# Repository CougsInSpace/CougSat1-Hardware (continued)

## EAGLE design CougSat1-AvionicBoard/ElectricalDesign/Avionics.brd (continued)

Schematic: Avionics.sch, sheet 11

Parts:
C13, C14, C27, C33, C36, C39: 100nF 10%; 1608
C17: 10nF 10%; 1608
C21, C25: 10pF 5%; 1608
C30, C32: 15pF 1%; 1608
DS1: Green; 1608-POL
J1: CougSat Card; CARD-FULL
J4: SWD; SMD2.54-1X06-R
R4, R12: 1kΩ 0.1%; 1608
R11: 0Ω <20mΩ; 1608
RT2: 10kΩ 5%; 1608
U6: STM32L476RGT; QFP-64-1010
U8, U9: TXS0102DQM; X2SON-8
Y2: 8MHz ±10ppm; SMD-5032
Y4: 32.768kHz ±10ppm; SMD-3215

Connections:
3.3V_0: C13.1, C14.1, C27.1, C33.1, C36.1, R12.2, U6.1 (VBAT), U6.13 (VDDA/VREF+), U6.19 (VDD), U6.32 (VDD), U6.48 (VDDUSB), U6.64 (VDD), U8.1 (VCCA), U9.1 (VCCA); also elsewhere on the board
3.3V_5: C39.1, U8.8 (VCCB), U9.8 (VCCB); also elsewhere on the board
!C&DH_ADC_RESET: U6.24 (PC4); also elsewhere on the board
AGND: RT2.1; also elsewhere on the board
BUS_I2C0_IRQ: J1.A45 (BUS_I2C0_IRQ), J1.B45 (BUS_I2C0_IRQ), U6.61 (PB8); also elsewhere on the board
BUS_I2C0_SCL: J1.A44 (BUS_I2C0_SCL), J1.B44 (BUS_I2C0_SCL), U6.58 (PB6); also elsewhere on the board
BUS_I2C0_SDA: J1.A43 (BUS_I2C0_SDA), J1.B43 (BUS_I2C0_SDA), U6.59 (PB7); also elsewhere on the board
BUS_I2C1_IRQ: J1.A32 (BUS_I2C1_IRQ), J1.B32 (BUS_I2C1_IRQ), U6.33 (PB12)
BUS_I2C1_SCL: J1.A31 (BUS_I2C1_SCL), J1.B31 (BUS_I2C1_SCL), U6.34 (PB13); also elsewhere on the board
BUS_I2C1_SDA: J1.A30 (BUS_I2C1_SDA), J1.B30 (BUS_I2C1_SDA), U6.30 (PB11); also elsewhere on the board
BUS_JTAG_TCK: U8.7 (B1); also elsewhere on the board
BUS_JTAG_TDI: U8.6 (B2); also elsewhere on the board
BUS_JTAG_TDO: U9.7 (B1); also elsewhere on the board
BUS_JTAG_TMS: U9.6 (B2); also elsewhere on the board
BUS_SPI_IFJR_CS: U6.43 (PA10); also elsewhere on the board
BUS_SPI_MISO: J1.A38 (BUS_SPI_MISO), J1.B38 (BUS_SPI_MISO), U6.22 (PA6); also elsewhere on the board
BUS_SPI_MOSI: J1.A39 (BUS_SPI_MOSI), J1.B39 (BUS_SPI_MOSI), U6.21 (PA5); also elsewhere on the board
BUS_SPI_SCK: J1.A37 (BUS_SPI_SCK), J1.B37 (BUS_SPI_SCK), U6.23 (PA7); also elsewhere on the board
COM_SPI_CS: J1.A36 (!COM_SPI_CS), J1.B36 (!COM_SPI_CS), U6.9 (PC1)
COM_SPI_MISO: J1.A34 (COM_SPI_MISO), J1.B34 (COM_SPI_MISO), U6.10 (PC2)
COM_SPI_MOSI: J1.A35 (COM_SPI_MOSI), J1.B35 (COM_SPI_MOSI), U6.11 (PC3)
COM_SPI_SCK: J1.A33 (COM_SPI_SCK), J1.B33 (COM_SPI_SCK), U6.29 (PB10)
CTRL_SYNC: J1.A42 (CTRL_SYNC), J1.B42 (CTRL_SYNC), U6.39 (PC8); also elsewhere on the board
DGND: C13.2, C14.2, C17.2, C21.2, C25.2, C27.2, C30.2, C32.2, C33.2, C36.2, C39.2, J4.3 (DGND), R4.2, R11.1, U6.12 (VSSA/VREF-), U6.18 (VSS), U6.31 (VSS), U6.47 (VSS), U6.63 (VSS), U8.4 (DGND), U9.4 (DGND), Y2.2 (GND), Y2.4 (GND); also elsewhere on the board
IHU_!NRST: C17.1, J4.5 (!RST), U6.7 (!NRST)
IHU_BOOT0: R11.2, U6.60 (BOOT0)
IHU_GPIO-0: J1.A24 (GPIO-0), U6.41 (PA8)
IHU_GPIO-1: J1.A25 (GPIO-1), U6.40 (PC9)
IHU_GPIO-2: J1.A26 (GPIO-2), U6.36 (PB15)
IHU_GPIO-3: J1.A27 (GPIO-3), U6.35 (PB14)
IHU_GPIO-4: J1.A28 (GPIO-4), U6.20 (PA4)
IHU_GPIO-5: J1.A29 (GPIO-5), U6.17 (PA3)
IHU_GPIO-6: J1.A41 (GPIO-6), U6.38 (PC7)
IHU_GPIO-7: J1.B41 (GPIO-7), U6.37 (PC6)
IHU_JTCK: J4.2 (SWCLK), U6.49 (PA14), U8.3 (A2)
IHU_JTDI: U6.50 (PA15), U8.2 (A1)
IHU_JTDO: J4.6 (SWO), U6.55 (PB3), U9.2 (A1)
IHU_JTMS: J4.4 (SWDIO), U6.46 (PA13), U9.3 (A2)
IHU_LED: DS1.A, U6.42 (PA9)
IHU_LED_GND: DS1.C, R4.1
IHU_OSC_32_IN: C30.1, U6.4 (PC15), Y4.1
IHU_OSC_32_OUT: C32.1, U6.3 (PC14), Y4.2
IHU_OSC_IN: C25.1, U6.5 (PH0-OSC_IN), Y2.1
IHU_OSC_OUT: C21.1, U6.6 (PH1-OSC_OUT), Y2.3 (2)
IHU_SD_CS0: U6.15 (PA1); also elsewhere on the board
IHU_SD_CS1: U6.14 (PA0); also elsewhere on the board
IHU_SD_SW0: U6.26 (PB0); also elsewhere on the board
IHU_SD_SW1: U6.28 (PB2); also elsewhere on the board
IHU_SPI_MISO: U6.52 (PC11); also elsewhere on the board
IHU_SPI_MOSI: U6.53 (PC12); also elsewhere on the board
IHU_SPI_SCK: U6.51 (PC10); also elsewhere on the board
IHU_SWD_VSENSE: J4.1 (VSENSE), R12.1
JTAG_EN_IHU: U8.5 (OE), U9.5 (OE); also elsewhere on the board
PR_3.3V-1: J1.A2 (PR_3.3V-1), J1.B2 (PR_3.3V-1)
PR_3.3V-3: J1.A4 (PR_3.3V-3), J1.B4 (PR_3.3V-3)
PR_3.3V-4: J1.A5 (PR_3.3V-4), J1.B5 (PR_3.3V-4)
PR_3.3V-6: J1.A7 (PR_3.3V-6), J1.B7 (PR_3.3V-6)
PR_3.3V-7: J1.A8 (PR_3.3V-7), J1.B8 (PR_3.3V-7)
PR_3.3V-8: J1.A9 (PR_3.3V-8), J1.B9 (PR_3.3V-8)
PR_3.3V-9: J1.A10 (PR_3.3V-9), J1.B10 (PR_3.3V-9)
PR_3.3V-10: J1.A11 (PR_3.3V-10), J1.B11 (PR_3.3V-10)
PR_3.3V-11: J1.A12 (PR_3.3V-11), J1.B12 (PR_3.3V-11)
PR_3.3V-12: J1.A13 (PR_3.3V-12), J1.B13 (PR_3.3V-12)
PR_BATT-0: J1.A14 (PR_BATT-0), J1.B14 (PR_BATT-0)
PR_BATT-1: J1.A15 (PR_BATT-1), J1.B15 (PR_BATT-1)
PR_BATT-2: J1.A16 (PR_BATT-2), J1.B16 (PR_BATT-2)
PR_BATT-3: J1.A17 (PR_BATT-3), J1.B17 (PR_BATT-3)
PR_BATT-4: J1.A18 (PR_BATT-4), J1.B18 (PR_BATT-4)
PR_BATT-6: J1.A20 (PR_BATT-6), J1.B20 (PR_BATT-6)
TEMP_IHU: RT2.2; also elsewhere on the board

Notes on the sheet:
11B6> 3C5>
<11B6><3C5>
11B6> 12C4>
<11B6><12C4>
<11B6>
<11C6>
<11B2
11B2>
12A3>
<12A3
<12B3
<11B3>
<11B3
<11B3
11B6>
<11B6
<11B4
11B4>
<11D1 <11C1
<11D6><11D1
11D6> 11D1>
<11B2>
11B6> 3B5> 9B3>
11A5>
<11B2
11B3>
<9B6
<11C1
CAD Note: Decoupling
11B2>
11C3>
CAD Note: Thermally Connected
12C1>
12C3>
9D3>
<11D6
CAD Note: Decoupling
<11C2
12B3>
<11B6 <9C3

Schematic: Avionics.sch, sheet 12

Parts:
C1, C5, C6, C7, C8, C26, C46: 100nF 10%; 1608
C2, C4: 1µF 10%; 1608
C3: 10µF 10%; 1608
C9: 4.7µF 10%; 4028-POL
FB1: 1.5kΩ @ 100MHz; 1608
J10: IHU SD0; µSD-PUSH-PUSH
J11: IHU SD1; µSD-PUSH-PUSH
R1, R5, R6: 10kΩ 0.1%; 1608
RN1: 10kΩ 5%; 3264
RT3, RT7: 10kΩ 5%; 1608
TP1: TEST_POINT-SMD-C-1.25; SMD-C-1.25
U1: AD7291; QFN-20-4040
U2: AD8515; SOT23-5

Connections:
3.3V_0: C7.1, C26.1, C46.1, FB1.1, J10.VDD, J11.VDD, R1.2, R5.2, R6.2, U1.13 (AS1), U1.16 (VDRIVE); also elsewhere on the board
!C&DH_ADC_RESET: R1.1, U1.17 (!PD!/!RST); also elsewhere on the board
AGND: C1.2, C2.2, C3.2, C5.2, C6.2, C8.2, C9.C, RT3.1, RT7.1, U1.6 (AGND), U2.2 (V-); also elsewhere on the board
AVDD-1: C5.1, C6.1, C8.1, C9.A, FB1.2, TP1.1, U1.10 (VDD), U2.5 (V+)
AVREF-2: C1.1, C2.1, RN1.5 (C), RN1.10 (C), U2.1 (OUT), U2.4 (IN-)
BUS_I2C1_SCL: U1.15 (SCL); also elsewhere on the board
BUS_I2C1_SDA: U1.14 (SDA); also elsewhere on the board
C&DH_ADC_DCAP: C4.1, U1.8 (DCAP)
C&DH_ADC_VREF: C3.1, U1.7 (VREF), U2.3 (IN+)
DGND: C4.2, C7.2, C26.2, C46.2, J10.SW-LEVER (SW-), J10.VSS, J11.SW-LEVER (SW-), J11.VSS, U1.4 (IN6), U1.5 (IN7), U1.9 (DGND), U1.11 (AS0), U1.PAD (DGND); also elsewhere on the board
IHU_SD_CS0: J10.CD/DAT3, R5.1; also elsewhere on the board
IHU_SD_CS1: J11.CD/DAT3, R6.1; also elsewhere on the board
IHU_SD_SW0: J10.SW (SW+); also elsewhere on the board
IHU_SD_SW1: J11.SW (SW+); also elsewhere on the board
IHU_SPI_MISO: J10.DAT0, J11.DAT0; also elsewhere on the board
IHU_SPI_MOSI: J10.CMD, J11.CMD; also elsewhere on the board
IHU_SPI_SCK: J10.CLK, J11.CLK; also elsewhere on the board
TEMP_IFJR: RN1.8 (7), U1.19 (IN1); also elsewhere on the board
TEMP_IHU: RN1.9 (8), U1.18 (IN0); also elsewhere on the board
TEMP_SD_IFJR0: RN1.4, U1.2 (IN4); also elsewhere on the board
TEMP_SD_IFJR1: RN1.3, U1.3 (IN5); also elsewhere on the board
TEMP_SD_IHU0: RN1.7 (6), RT3.2, U1.20 (IN2)
TEMP_SD_IHU1: RN1.6 (5), RT7.2, U1.1 (IN3)

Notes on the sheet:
<11B4
11B4>
<11B2
11B3>
CAD Note: Thermally Connected
12C1>
CAD Note: Decoupling
<11B3>
<11B3
11A6>
9A6>
12A4>
12B4>
10B6>
10C6>

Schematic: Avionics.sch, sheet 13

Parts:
J1: CougSat Card; CARD-FULL
J2: -X; PICOLOCK1.5-04
J3: +Z; PICOLOCK1.5-04
J5: +Y; PICOLOCK1.5-04
J6: -Y; PICOLOCK1.5-04
J9: -Z; PICOLOCK1.5-04
J15: +X; PICOLOCK1.5-04

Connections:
3.3V_0: J1.A1 (PR_3.3V-0), J1.B1 (PR_3.3V-0); also elsewhere on the board
3.3V_2: J1.A3 (PR_3.3V-2), J1.B3 (PR_3.3V-2), J9.3, J15.3; also elsewhere on the board
3.3V_5: J1.A6 (PR_3.3V-5), J1.B6 (PR_3.3V-5); also elsewhere on the board
ADCS_I2C1_SCL: J2.1, J3.1, J5.1, J6.1, J9.1, J15.1; also elsewhere on the board
ADCS_I2C1_SDA: J2.2, J3.2, J5.2, J6.2, J9.2, J15.2; also elsewhere on the board
CHASSIS: J1.CHASSIS@1 (CHASSIS), J1.CHASSIS@2 (CHASSIS), J1.CHASSIS@3 (CHASSIS), J1.CHASSIS@4 (CHASSIS); also elsewhere on the board
COIL-X_COIL+: J2.3; also elsewhere on the board
COIL-X_COIL-: J2.4; also elsewhere on the board
COIL-Y_COIL+: J5.3, J6.3; also elsewhere on the board
COIL-Y_COIL-: J5.4, J6.4; also elsewhere on the board
COIL-Z_COIL+: J3.3; also elsewhere on the board
COIL-Z_COIL-: J3.4; also elsewhere on the board
DGND: J9.4, J15.4; also elsewhere on the board
PGND: J1.A21 (PGND), J1.A22 (PGND), J1.A23 (PGND), J1.B21 (PGND), J1.B22 (PGND), J1.B23 (PGND), J1.B24 (PGND), J1.B25 (PGND), J1.B26 (PGND), J1.B27 (PGND), J1.B28 (PGND), J1.B29 (PGND); also elsewhere on the board
PR_3.3V-1: J1.A2 (PR_3.3V-1), J1.B2 (PR_3.3V-1)
PR_3.3V-3: J1.A4 (PR_3.3V-3), J1.B4 (PR_3.3V-3)
PR_3.3V-4: J1.A5 (PR_3.3V-4), J1.B5 (PR_3.3V-4)
PR_3.3V-6: J1.A7 (PR_3.3V-6), J1.B7 (PR_3.3V-6)
PR_3.3V-7: J1.A8 (PR_3.3V-7), J1.B8 (PR_3.3V-7)
PR_3.3V-8: J1.A9 (PR_3.3V-8), J1.B9 (PR_3.3V-8)
PR_3.3V-9: J1.A10 (PR_3.3V-9), J1.B10 (PR_3.3V-9)
PR_3.3V-10: J1.A11 (PR_3.3V-10), J1.B11 (PR_3.3V-10)
PR_3.3V-11: J1.A12 (PR_3.3V-11), J1.B12 (PR_3.3V-11)
PR_3.3V-12: J1.A13 (PR_3.3V-12), J1.B13 (PR_3.3V-12)
PR_BATT-0: J1.A14 (PR_BATT-0), J1.B14 (PR_BATT-0)
PR_BATT-1: J1.A15 (PR_BATT-1), J1.B15 (PR_BATT-1)
PR_BATT-2: J1.A16 (PR_BATT-2), J1.B16 (PR_BATT-2)
PR_BATT-3: J1.A17 (PR_BATT-3), J1.B17 (PR_BATT-3)
PR_BATT-4: J1.A18 (PR_BATT-4), J1.B18 (PR_BATT-4)
PR_BATT-6: J1.A20 (PR_BATT-6), J1.B20 (PR_BATT-6)
VBATT_5: J1.A19 (PR_BATT-5), J1.B19 (PR_BATT-5); also elsewhere on the board

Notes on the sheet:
<5A5
<5B5
<5C5
5C5>
5B5>
5A5>
<3B5
<3B5>

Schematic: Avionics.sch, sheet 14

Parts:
J1: CougSat Card; CARD-FULL
LOGO1: SIGNATUREGABE; SIGN-GABE

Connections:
PR_3.3V-1: J1.A2 (PR_3.3V-1), J1.B2 (PR_3.3V-1)
PR_3.3V-3: J1.A4 (PR_3.3V-3), J1.B4 (PR_3.3V-3)
PR_3.3V-4: J1.A5 (PR_3.3V-4), J1.B5 (PR_3.3V-4)
PR_3.3V-6: J1.A7 (PR_3.3V-6), J1.B7 (PR_3.3V-6)
PR_3.3V-7: J1.A8 (PR_3.3V-7), J1.B8 (PR_3.3V-7)
PR_3.3V-8: J1.A9 (PR_3.3V-8), J1.B9 (PR_3.3V-8)
PR_3.3V-9: J1.A10 (PR_3.3V-9), J1.B10 (PR_3.3V-9)
PR_3.3V-10: J1.A11 (PR_3.3V-10), J1.B11 (PR_3.3V-10)
PR_3.3V-11: J1.A12 (PR_3.3V-11), J1.B12 (PR_3.3V-11)
PR_3.3V-12: J1.A13 (PR_3.3V-12), J1.B13 (PR_3.3V-12)
PR_BATT-0: J1.A14 (PR_BATT-0), J1.B14 (PR_BATT-0)
PR_BATT-1: J1.A15 (PR_BATT-1), J1.B15 (PR_BATT-1)
PR_BATT-2: J1.A16 (PR_BATT-2), J1.B16 (PR_BATT-2)
PR_BATT-3: J1.A17 (PR_BATT-3), J1.B17 (PR_BATT-3)
PR_BATT-4: J1.A18 (PR_BATT-4), J1.B18 (PR_BATT-4)
PR_BATT-6: J1.A20 (PR_BATT-6), J1.B20 (PR_BATT-6)

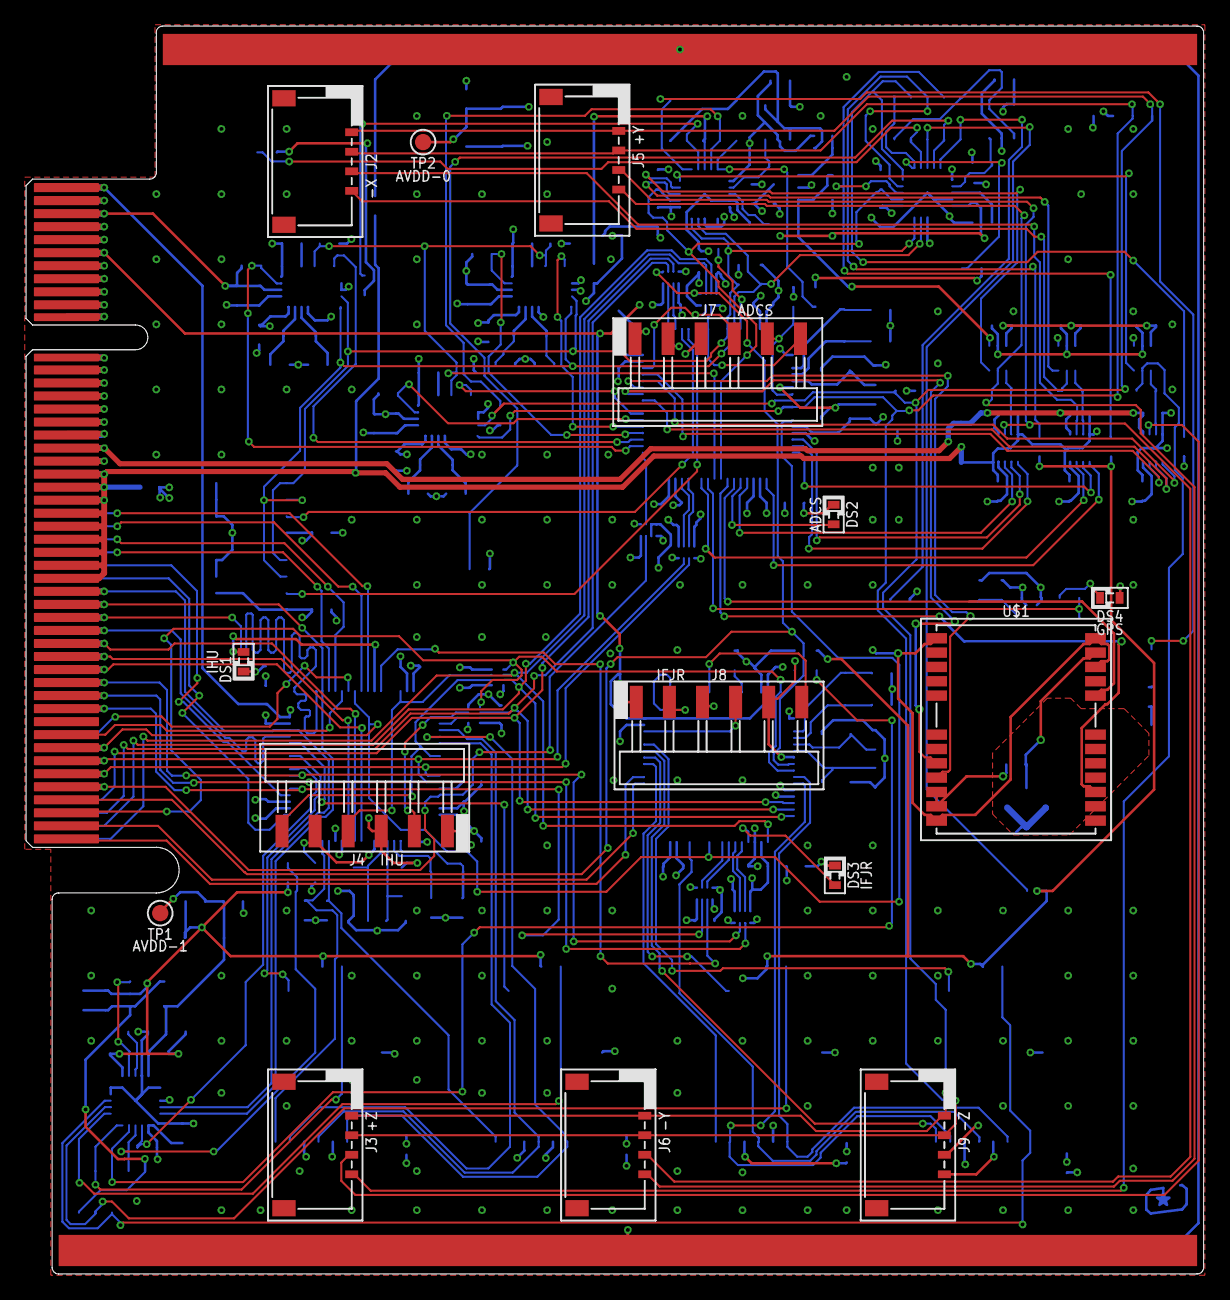
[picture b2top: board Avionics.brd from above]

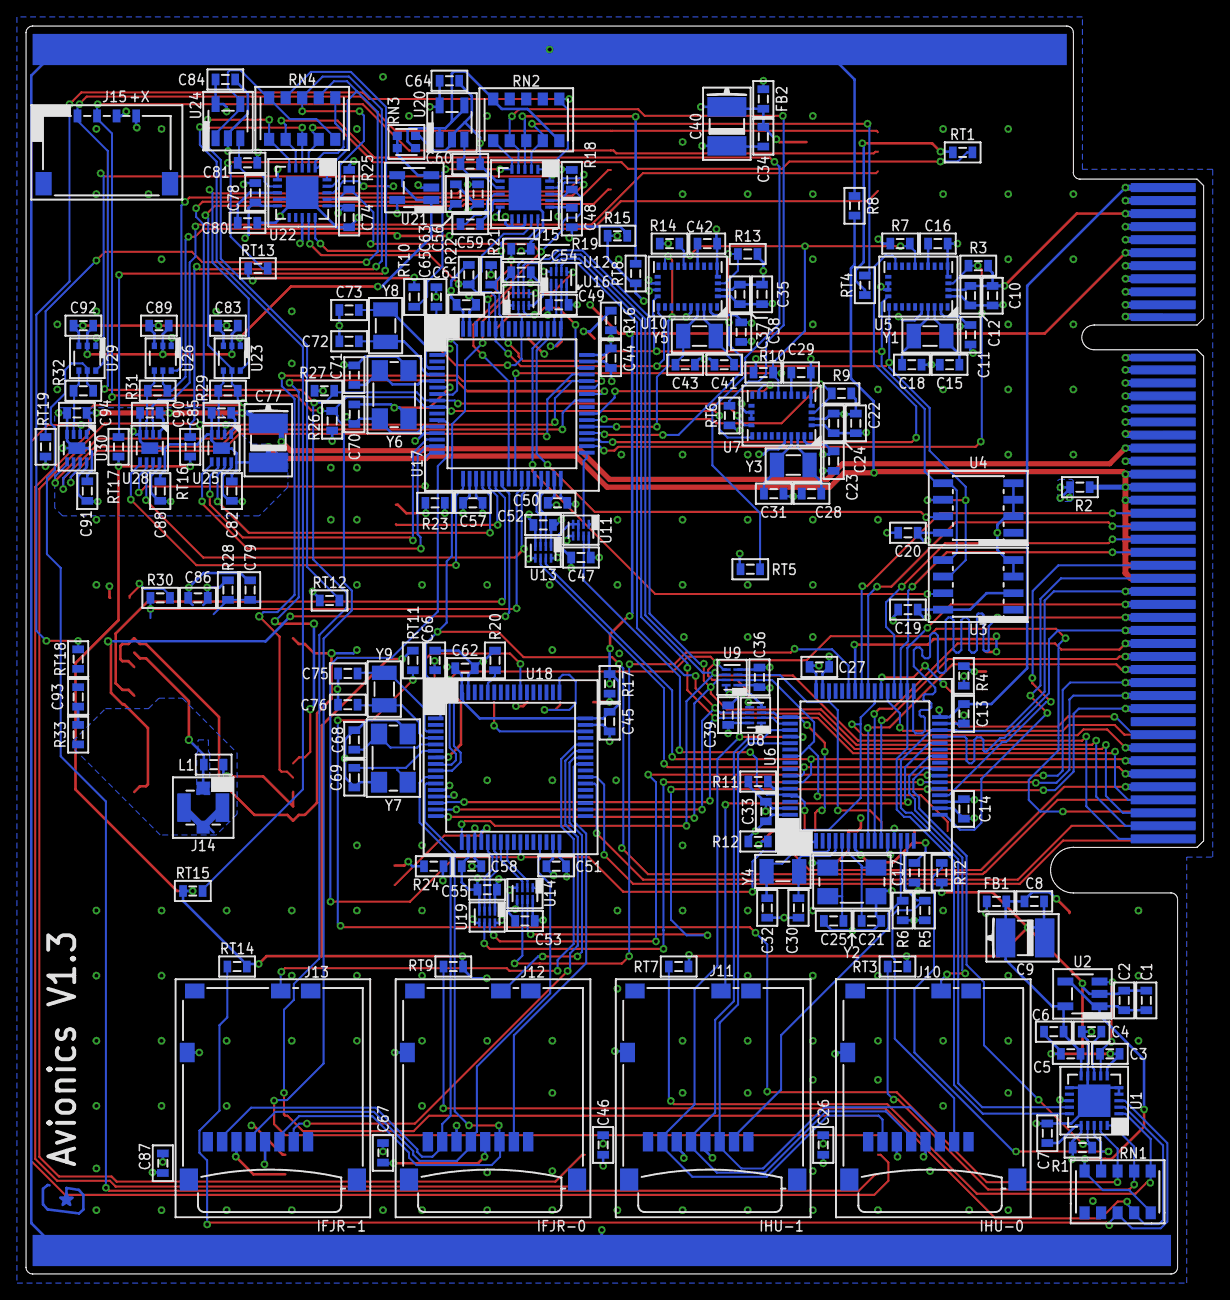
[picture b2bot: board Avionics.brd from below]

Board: 4 copper layers, 90.4 x 95.8 mm, 214 parts (198 on the bottom side), 199 nets.

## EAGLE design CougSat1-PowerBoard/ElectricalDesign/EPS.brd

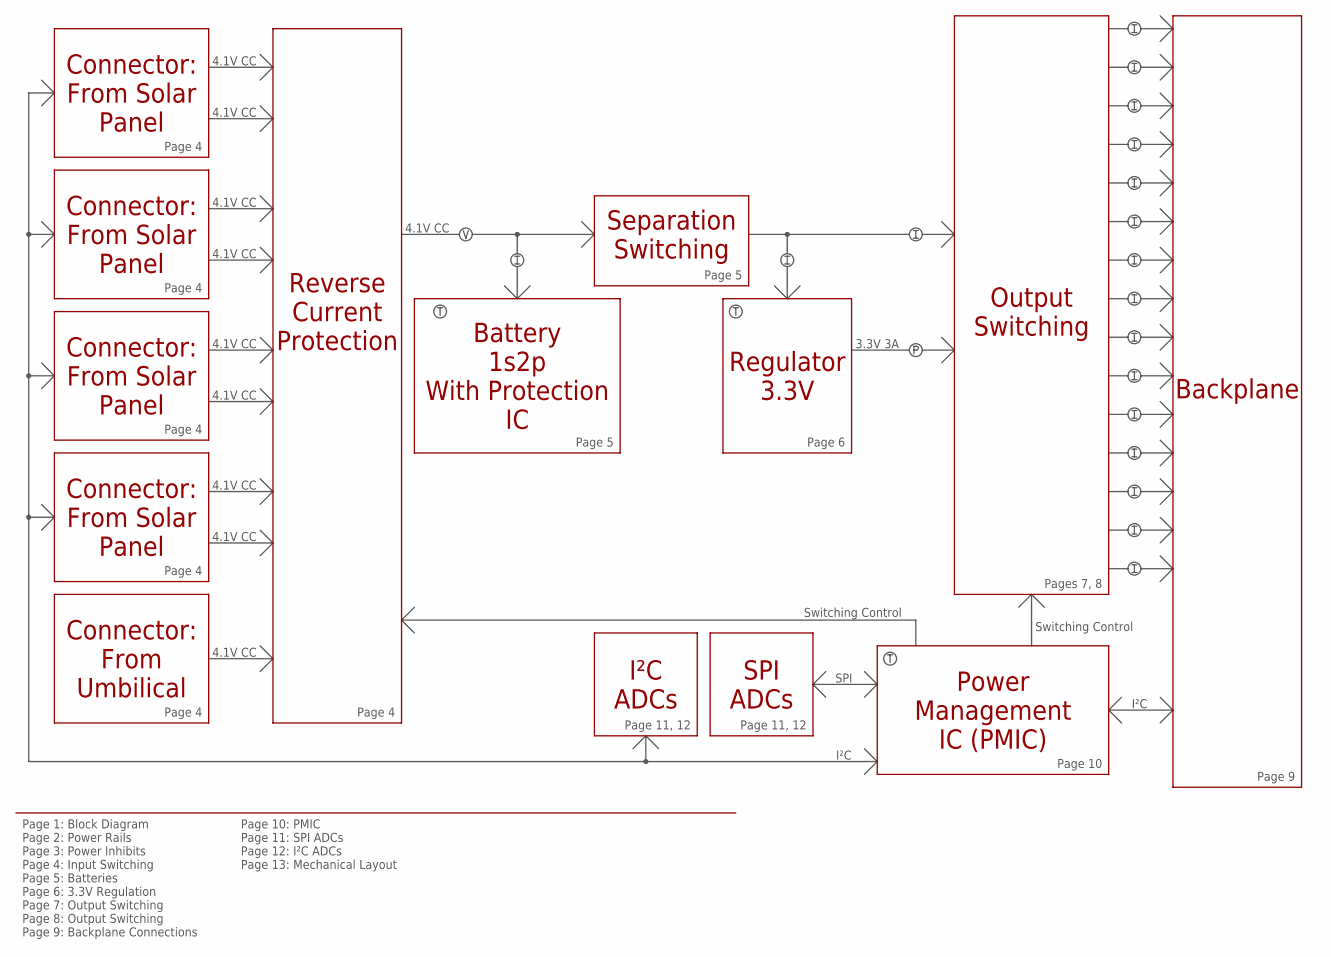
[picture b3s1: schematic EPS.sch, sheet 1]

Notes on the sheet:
Connector: From Solar Panel
Reverse Current Protection
Regulator 3.3V
Backplane
Power Management IC (PMIC)
I²C
Switching Control
4.1V CC
3.3V 3A
Page 4
Page 5
Page 6
Pages 7, 8
Page 9
Page 10
Page 11, 12
I²C ADCs
Page 1: Block Diagram Page 2: Power Rails Page 3: Power Inhibits Page 4: Input Switching Page 5: Batteries Page 6: 3.3V Regulation Page 7: Output Switching Page 8: Output Switching Page 9: Backplane Connections
Separation Switching
Connector: From Umbilical
Battery 1s2p With Protection IC
Page 10: PMIC Page 11: SPI ADCs Page 12: I²C ADCs Page 13: Mechanical Layout
SPI ADCs
SPI
Output Switching

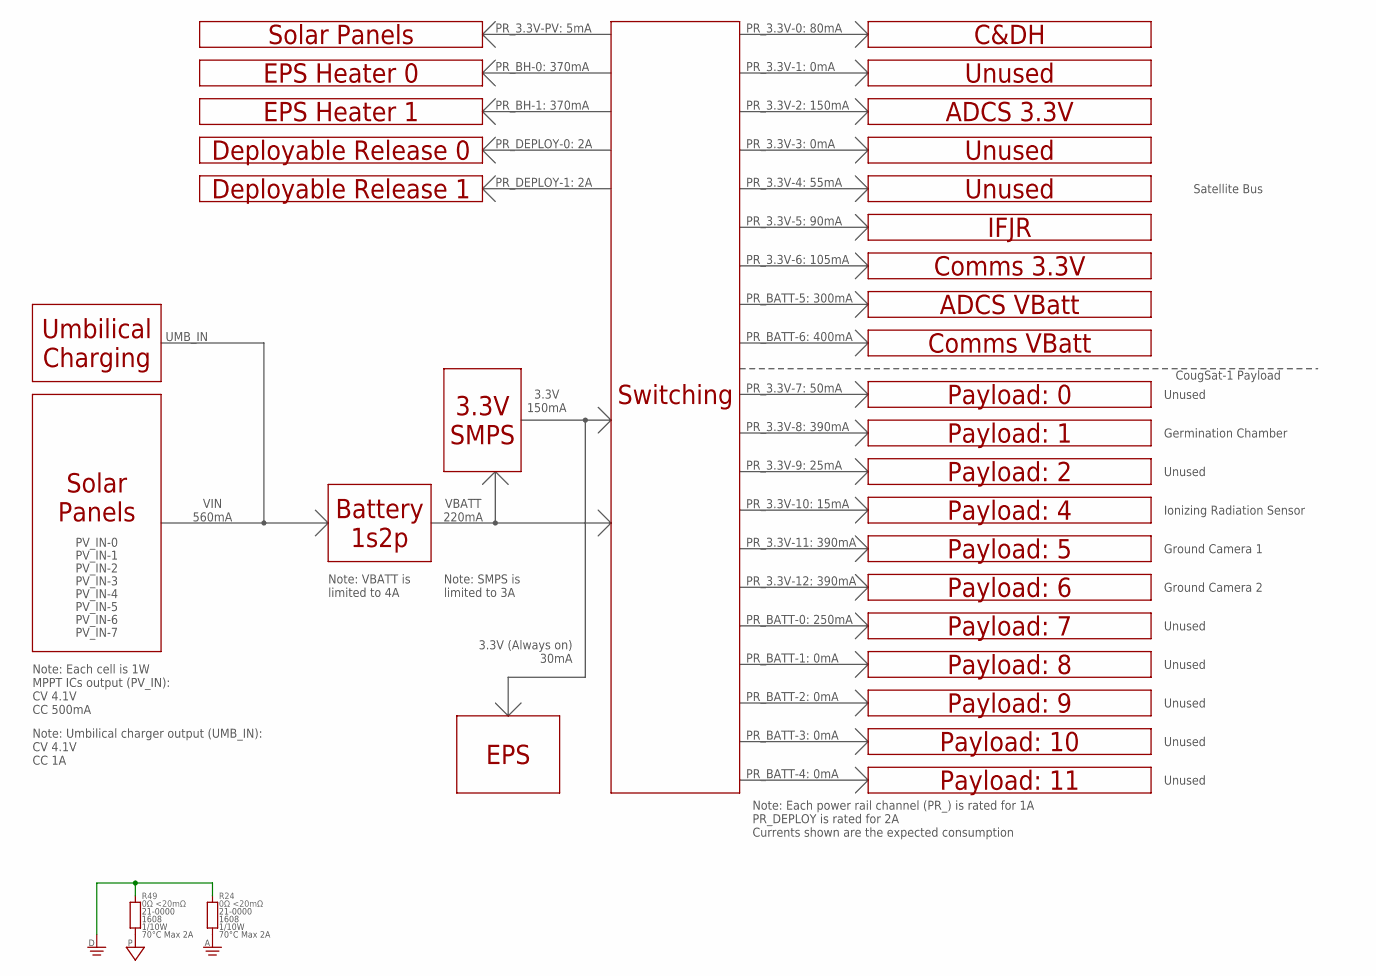
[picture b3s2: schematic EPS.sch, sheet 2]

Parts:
R24, R49: 0Ω <20mΩ; 1608

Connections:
AGND: R24.1; also elsewhere on the board
DGND: R24.2, R49.2; also elsewhere on the board
PGND: R49.1; also elsewhere on the board

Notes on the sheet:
Solar Panels
Battery 1s2p
3.3V SMPS
EPS
3.3V (Always on) 30mA
C&DH
PR_3.3V-0: 80mA
Unused
PR_3.3V-1: 0mA
ADCS 3.3V
PR_3.3V-2: 150mA
PR_3.3V-3: 0mA
PR_3.3V-4: 55mA
ADCS VBatt
PR_BATT-5: 300mA
IFJR
PR_3.3V-5: 90mA
Payload: 10
PR_BATT-6: 400mA
Payload: 9
PR_BATT-2: 0mA
Comms 3.3V
PR_3.3V-6: 105mA
Comms VBatt
PR_BATT-3: 0mA
Payload: 0
PR_3.3V-7: 50mA
Payload: 1
PR_3.3V-8: 390mA
Payload: 2
PR_3.3V-9: 25mA
Payload: 7
PR_BATT-0: 250mA
Payload: 4
PR_3.3V-10: 15mA
Payload: 5
PR_3.3V-11: 390mA
Payload: 11
PR_BATT-4: 0mA
Germination Chamber

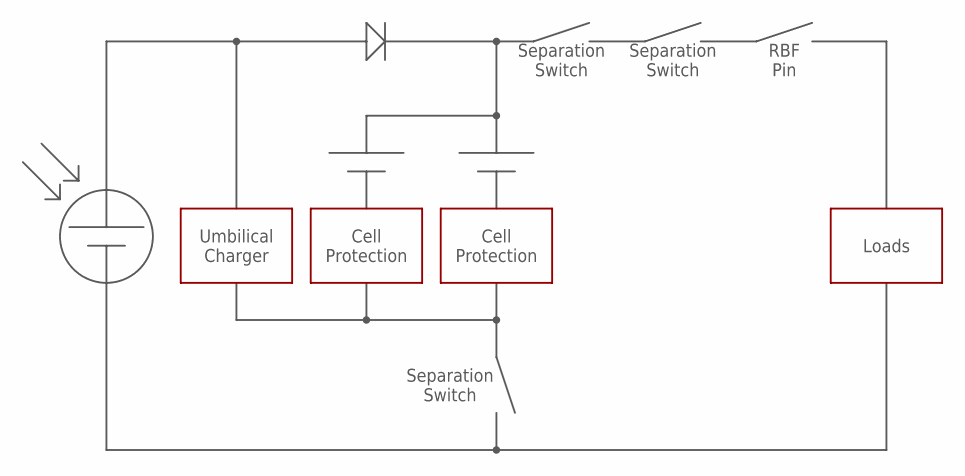
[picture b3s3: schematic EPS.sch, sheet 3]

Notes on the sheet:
Cell Protection
Umbilical Charger
Separation Switch
RBF Pin
Loads

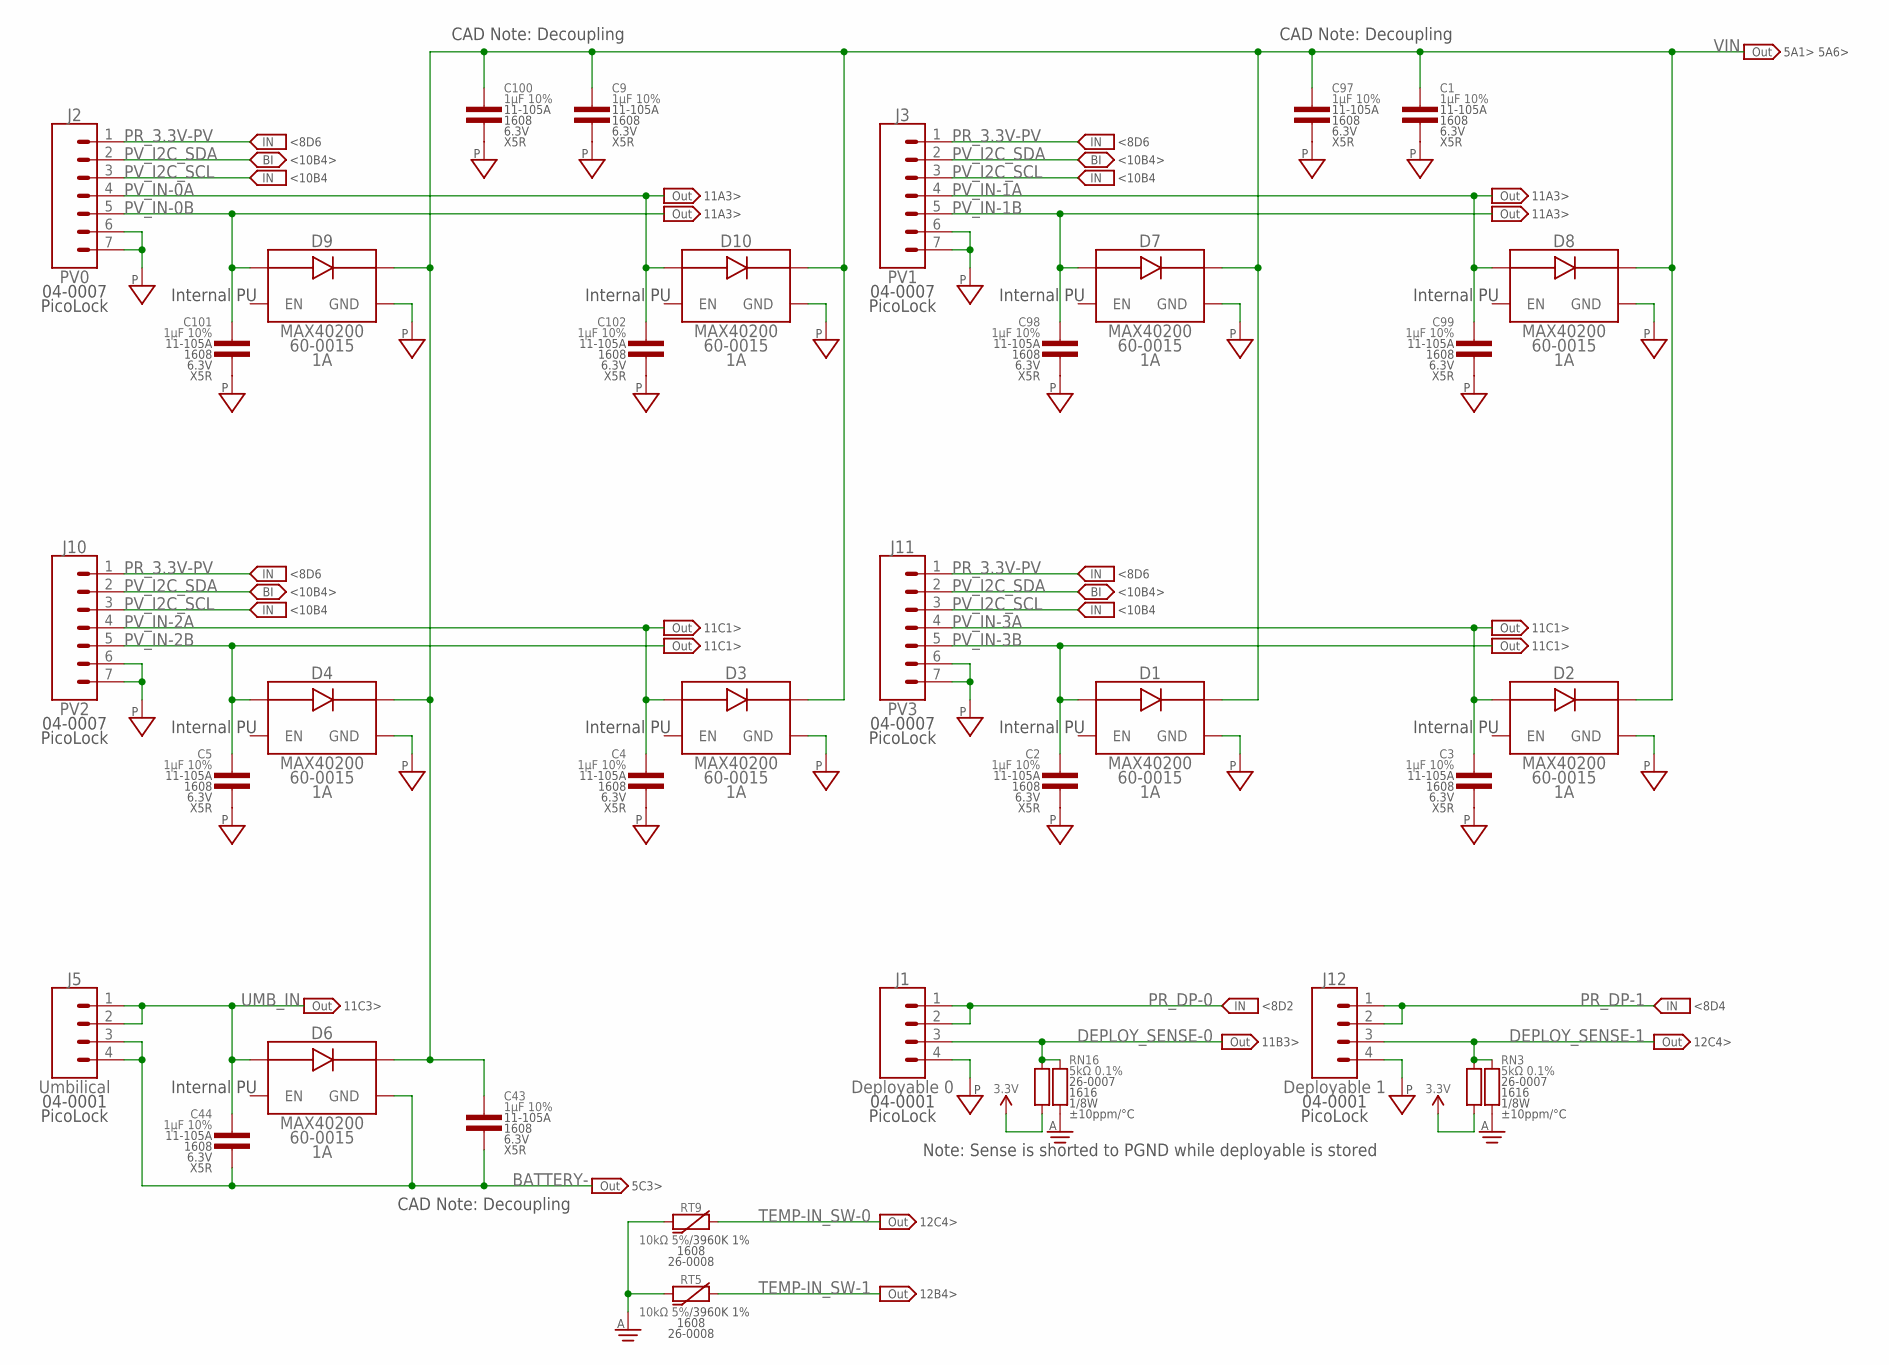
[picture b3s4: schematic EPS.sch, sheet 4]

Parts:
C1, C2, C3, C4, C5, C9, C43, C44, C97, C98, C99, C100, C101, C102: 1µF 10%; 1608
D1, D2, D3, D4, D6, D7, D8, D9, D10: MAX40200; SOT23-5
J1: Deployable 0; PICOLOCK1.5-04
J2: PV0; PICOLOCK1.5-07
J3: PV1; PICOLOCK1.5-07
J5: Umbilical; PICOLOCK1.5-04
J10: PV2; PICOLOCK1.5-07
J11: PV3; PICOLOCK1.5-07
J12: Deployable 1; PICOLOCK1.5-04
RN3, RN16: 5kΩ 0.1%; 1616
RT5, RT9: 10kΩ 5%; 1608

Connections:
3.3V: RN3.2 (B1), RN16.2 (B1); also elsewhere on the board
AGND: RN3.1 (A1), RN16.1 (A1), RT5.1, RT9.1; also elsewhere on the board
BATTERY-: C43.2, C44.2, D6.2 (GND), J5.3, J5.4; also elsewhere on the board
DEPLOY_SENSE-0: J1.3, RN16.3 (B2), RN16.4 (A2); also elsewhere on the board
DEPLOY_SENSE-1: J12.3, RN3.3 (B2), RN3.4 (A2); also elsewhere on the board
PGND: C1.2, C2.2, C3.2, C4.2, C5.2, C9.2, C97.2, C98.2, C99.2, C100.2, C101.2, C102.2, D1.2 (GND), D2.2 (GND), D3.2 (GND), D4.2 (GND), D7.2 (GND), D8.2 (GND), D9.2 (GND), D10.2 (GND), J1.4, J2.6, J2.7, J3.6, J3.7, J10.6, J10.7, J11.6, J11.7, J12.4; also elsewhere on the board
PR_3.3V-PV: J2.1, J3.1, J10.1, J11.1; also elsewhere on the board
PR_DP-0: J1.1, J1.2; also elsewhere on the board
PR_DP-1: J12.1, J12.2; also elsewhere on the board
PV_I2C_SCL: J2.3, J3.3, J10.3, J11.3; also elsewhere on the board
PV_I2C_SDA: J2.2, J3.2, J10.2, J11.2; also elsewhere on the board
PV_IN-0A: C102.1, D10.1 (IN), J2.4; also elsewhere on the board
PV_IN-0B: C101.1, D9.1 (IN), J2.5; also elsewhere on the board
PV_IN-1A: C99.1, D8.1 (IN), J3.4; also elsewhere on the board
PV_IN-1B: C98.1, D7.1 (IN), J3.5; also elsewhere on the board
PV_IN-2A: C4.1, D3.1 (IN), J10.4; also elsewhere on the board
PV_IN-2B: C5.1, D4.1 (IN), J10.5; also elsewhere on the board
PV_IN-3A: C3.1, D2.1 (IN), J11.4; also elsewhere on the board
PV_IN-3B: C2.1, D1.1 (IN), J11.5; also elsewhere on the board
TEMP-IN_SW-0: RT9.2; also elsewhere on the board
TEMP-IN_SW-1: RT5.2; also elsewhere on the board
UMB_IN: C44.1, D6.1 (IN), J5.1, J5.2; also elsewhere on the board
VIN: C1.1, C9.1, C43.1, C97.1, C100.1, D1.5 (OUT), D2.5 (OUT), D3.5 (OUT), D4.5 (OUT), D6.5 (OUT), D7.5 (OUT), D8.5 (OUT), D9.5 (OUT), D10.5 (OUT); also elsewhere on the board

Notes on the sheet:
Note: Sense is shorted to PGND while deployable is stored
CAD Note: Decoupling
Internal PU
5A1> 5A6>
<8D6
<10B4
<10B4>
11A3>
11C1>
11C3>
5C3>
11B3>
12C4>
12B4>
<8D2
<8D4

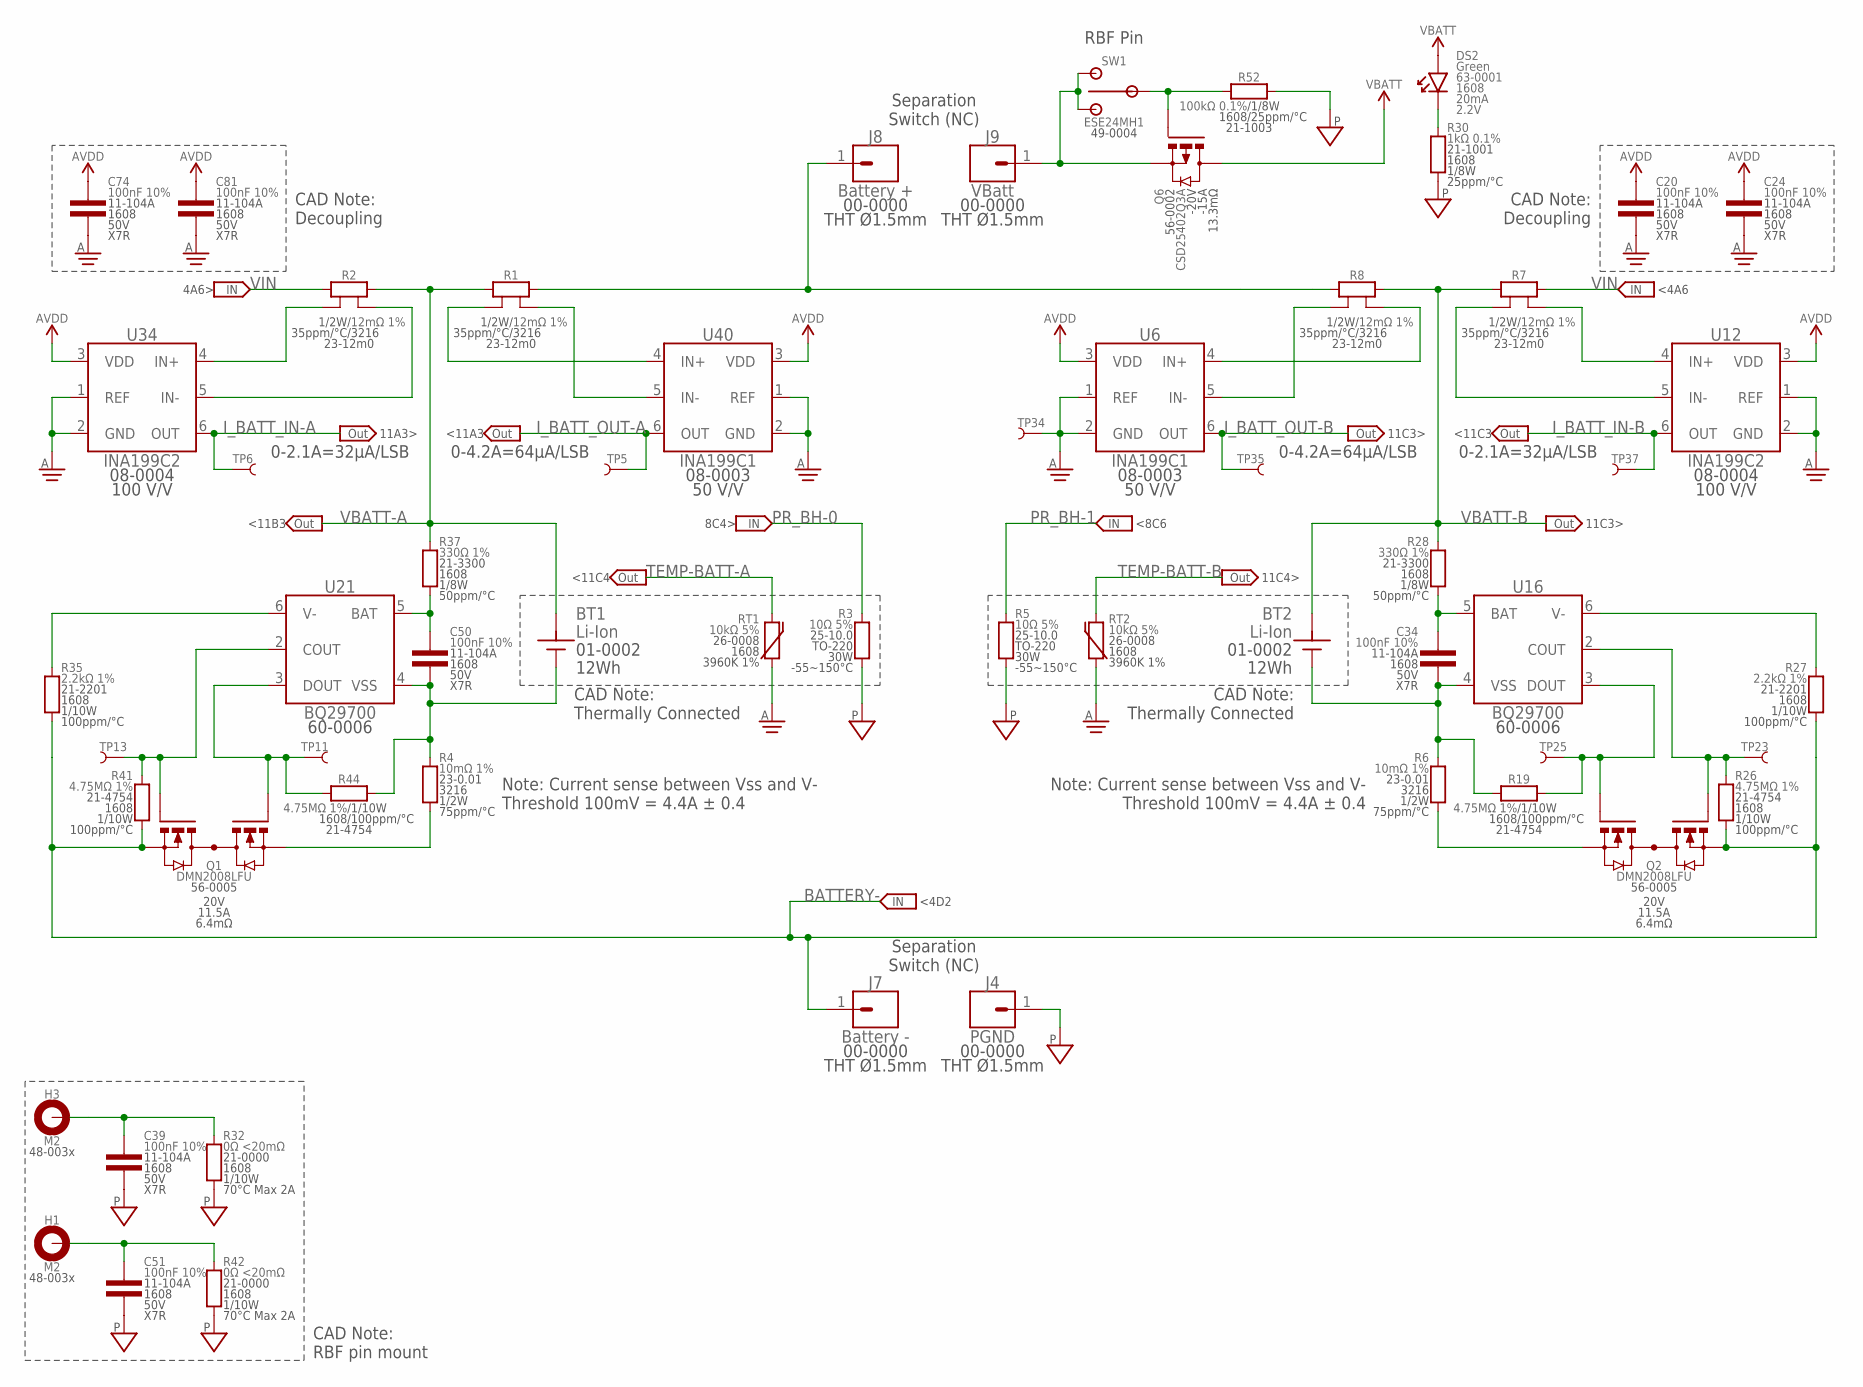
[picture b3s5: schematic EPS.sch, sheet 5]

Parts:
BT1, BT2: Li-Ion; 18650-SOLDERED
C20, C24, C34, C39, C50, C51, C74, C81: 100nF 10%; 1608
DS2: Green; 1608-POL
H1, H3: M2; MOUNTING_HOLE-2.2
J4: PGND; THT-1.5
J7: Battery -; THT-1.5
J8: Battery +; THT-1.5
J9: VBatt; THT-1.5
Q1, Q2: DMN2008LFU; UDFN-6-B
Q6: CSD25402Q3A; SON-3333
R1, R2, R7, R8: 12mΩ 1%; 3216-KELVIN
R3, R5: 10Ω 5%; TO-220-2
R4, R6: 10mΩ 1%; 3216
R19, R26, R41, R44: 4.75MΩ 1%; 1608
R27, R35: 2.2kΩ 1%; 1608
R28, R37: 330Ω 1%; 1608
R30: 1kΩ 0.1%; 1608
R32, R42: 0Ω <20mΩ; 1608
R52: 100kΩ 0.1%; 1608
RT1, RT2: 10kΩ 5%; 1608
SW1: ESE24MH1
TP5, TP6, TP11, TP13, TP23, TP25, TP34, TP35, TP37: TEST_POINT-SMD-C-1.25; SMD-C-1.25
U6, U40: INA199C1; SOT363
U12, U34: INA199C2; SOT363
U16, U21: BQ29700; WSON-6

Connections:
AGND: C20.2, C24.2, C74.2, C81.2, RT1.1, RT2.1, TP34.1, U6.1 (REF), U6.2 (GND), U12.1 (REF), U12.2 (GND), U34.1 (REF), U34.2 (GND), U40.1 (REF), U40.2 (GND); also elsewhere on the board
AVDD: C20.1, C24.1, C74.1, C81.1, U6.3 (VDD), U12.3 (VDD), U34.3 (VDD), U40.3 (VDD); also elsewhere on the board
BATTERY+: J8.1, R1.1, R8.2
BATTERY-: J7.1, Q1.1 (S1), Q2.6 (S2), R26.1, R27.1, R35.1, R41.1; also elsewhere on the board
BATT_PROTECT_BAT-A: C50.1, R37.1, U21.5 (BAT)
BATT_PROTECT_BAT-B: C34.1, R28.1, U16.5 (BAT)
BATT_PROTECT_COUT-A: Q1.3 (G1), R41.2, TP13.1, U21.2 (COUT)
BATT_PROTECT_COUT-B: Q2.4 (G2), R26.2, TP23.1, U16.2 (COUT)
BATT_PROTECT_DOUT-A: Q1.4 (G2), R44.1, TP11.1, U21.3 (DOUT)
BATT_PROTECT_DOUT-B: Q2.3 (G1), R19.2, TP25.1, U16.3 (DOUT)
BATT_PROTECT_GND-A: R35.2, U21.6 (V-)
BATT_PROTECT_GND-B: R27.2, U16.6 (V-)
BP_VSS-A: BT1.A, C50.2, R4.2, R44.2, U21.4 (VSS)
BP_VSS-B: BT2.A, C34.2, R6.2, R19.1, U16.4 (VSS)
BP_VSS_I-A: Q1.6 (S2), R4.1
BP_VSS_I-B: Q2.1 (S1), R6.1
CHASSIS_RBF0: C39.1, H3.1, H3.V1, H3.V2, H3.V3, H3.V4, H3.V5, H3.V6, H3.V7, H3.V8, R32.2
CHASSIS_RBF1: C51.1, H1.1, H1.V1, H1.V2, H1.V3, H1.V4, H1.V5, H1.V6, H1.V7, H1.V8, R42.2
I_BATT_IN-A: TP6.1, U34.6 (OUT); also elsewhere on the board
I_BATT_IN-A_N: R2.1-KELVIN, U34.5 (IN-)
I_BATT_IN-A_P: R2.2-KELVIN, U34.4 (IN+)
I_BATT_IN-B: TP37.1, U12.6 (OUT); also elsewhere on the board
I_BATT_IN-B_N: R7.2-KELVIN, U12.5 (IN-)
I_BATT_IN-B_P: R7.1-KELVIN, U12.4 (IN+)
I_BATT_OUT-A: TP5.1, U40.6 (OUT); also elsewhere on the board
I_BATT_OUT-A_N: R1.1-KELVIN, U40.5 (IN-)
I_BATT_OUT-A_P: R1.2-KELVIN, U40.4 (IN+)
I_BATT_OUT-B: TP35.1, U6.6 (OUT); also elsewhere on the board
I_BATT_OUT-B_N: R8.2-KELVIN, U6.5 (IN-)
I_BATT_OUT-B_P: R8.1-KELVIN, U6.4 (IN+)
PGND: C39.2, C51.2, J4.1, R3.1, R5.1, R30.1, R32.1, R42.1, R52.2; also elsewhere on the board
PR_BH-0: R3.3 (2); also elsewhere on the board
PR_BH-1: R5.3 (2); also elsewhere on the board
RBF_GATE: Q6.4 (G), R52.1, SW1.C
TEMP-BATT-A: RT1.2; also elsewhere on the board
TEMP-BATT-B: RT2.2; also elsewhere on the board
VBATT: DS2.A, Q6.1 (D), Q6.2 (D), Q6.3 (D); also elsewhere on the board
VBATT-A: BT1.C, R1.2, R2.1, R37.2; also elsewhere on the board
VBATT-B: BT2.C, R7.2, R8.1, R28.2; also elsewhere on the board
VBATT_LED: DS2.C, R30.2
VBATT_RBF: J9.1, Q6.5 (S), Q6.6 (S), Q6.7 (S), Q6.8 (S), Q6.PAD (S), SW1.1, SW1.2
VIN: R2.2, R7.1; also elsewhere on the board

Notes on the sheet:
CAD Note: Thermally Connected
CAD Note: RBF pin mount
Note: Current sense between Vss and V- Threshold 100mV = 4.4A ± 0.4
CAD Note: Decoupling
0-4.2A=64µA/LSB
0-2.1A=32µA/LSB
Separation Switch (NC)
RBF Pin
<4A6
<4D2
11C3>
<8C6
11A3>
11C4>
4A6>
8C4>
<11A3
<11C3
<11C4
<11B3
